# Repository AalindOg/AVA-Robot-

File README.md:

<div align="center">

# AVA — an AI companion with a physical body

**A wheeled robot project for [Half Life](https://halflife.hackclub.com) by Hack Club.**

Built by **Aalind Tiwari**, with AI-assisted CAD and development.

[Explore the CAD](cad/reference-rebuild/) · [Download STEP](https://github.com/AalindOg/AVA-Robot-/raw/refs/heads/main/cad/reference-rebuild/exports/AVA-reference-rebuild.step) · [View STL](cad/reference-rebuild/exports/AVA-reference-rebuild.stl) · [Development journal](JOURNAL.md)

*Actual renders of the current model. Not photographs of a fabricated robot.*

</div>

## What I’m building

AVA is a mobile AI companion: a screen for expression and interaction, cameras and microphones for sensing, speakers for responses, and a wheeled body. The longer-term goal is to connect that body to **Hermes Agent**, with a small controller handling the hardware interface and a computer handling higher-level processing.

This repository brings together three parts of that project: the **exterior CAD**, the **carrier-board design**, and the **firmware/server prototypes**. They are at different stages. The integrated, moving robot is not finished.

## Current milestone: a new body from the original references

The earlier STL attempt did not match the intended robot. Instead of polishing the wrong shape, this version was rebuilt from the original purple robot images and the surviving video views. The older meshes are not imported by the new model.

The design keeps the features that made the reference worth building:

- A **closed, rounded head** with a broad teal screen and thick bezel.
- Circular side grilles, flat antenna tabs and a low roof-mounted sensor housing.
- A curved torso with a narrower upper section, rounded lower body and dark panel trim.
- Two large treaded wheels with swept-spoke hubs.
- A small central twin-wheel caster, short side pods and a circular chest detail.

*Reference and reconstruction side by side. Fine seams, hidden surfaces and small hardware details are still approximate.*

> [!IMPORTANT]
> **This is an exterior design prototype, not a print-ready robot kit.** The STL files are real geometry exports, but the dimensions are image-based assumptions. Motor mounts, electronics packaging, joints, tolerances and print orientations still need engineering and physical tests. Do not print the complete assembly expecting a working robot.

## Get the files

| File | Use it for |
| --- | --- |
| [**Full STEP assembly**](https://github.com/AalindOg/AVA-Robot-/raw/refs/heads/main/cad/reference-rebuild/exports/AVA-reference-rebuild.step) | Import named, coloured solid components into FreeCAD, Fusion or Onshape. |
| [**Full STL assembly**](cad/reference-rebuild/exports/AVA-reference-rebuild.stl) | Inspect the complete geometry; this is a multi-component assembly, not one fused print. |
| [**Individual STL components**](cad/reference-rebuild/exports/parts/) | Inspect or modify separate shell sections, wheels, trim and other components. |
| [**Coloured GLB model**](https://github.com/AalindOg/AVA-Robot-/raw/refs/heads/main/cad/reference-rebuild/exports/AVA-reference-rebuild.glb) | Open in a compatible 3D viewer. Uses metres and +Y up. |
| [**CadQuery source**](cad/reference-rebuild/cad/build_robot.py) | Edit the construction and regenerate the geometry. |
| [**Design notes**](cad/reference-rebuild/DESIGN-NOTES.md) | Read the assumptions, interpretation choices and verification scope. |
| [**Printing status**](cad/reference-rebuild/PRINTING.md) | See what must be resolved before a physical prototype. |

For everything, use GitHub’s **Code → Download ZIP**, or clone this repository. STEP/STL use millimetres. STEP contains editable solids; the procedural construction lives in the Python source, not a native CAD feature-history tree.

## What has actually been checked

The current CAD export contains **38 component instances**. They include visual stand-ins for screens, sensors and axles—not 38 fabrication-ready parts.

| Check | Recorded result | Evidence |
| --- | --- | --- |
| Solid geometry | All 38 component instances valid, with positive volume | [Geometry report](cad/reference-rebuild/exports/validation.json) |
| Component clashes | No intersections above the **0.5 mm³** reporting threshold; no check errors | [Pairwise check](cad/reference-rebuild/exports/validation.json) |
| STL quality | Every individual STL is watertight, consistently wound, finite and positive-volume | [Mesh report](cad/reference-rebuild/exports/mesh-validation.json) |
| STEP round trip | Re-imported successfully; solid count and volume comparison passed | [Round-trip result](cad/reference-rebuild/exports/mesh-validation.json) |
| Viewer export | GLB re-imported with all 38 components | [Viewer check](cad/reference-rebuild/exports/mesh-validation.json) |
| Visual review | Front and angled views compared with the approved images | [Comparison sheet](cad/reference-rebuild/images/reference-comparison.jpg) |

The assumed exterior envelope is approximately **232 × 147 × 394 mm** (width × depth × height). Head width was set to **190 mm** as a scaling choice, not a measurement from a physical robot.

**These checks establish coherent files. They do not establish strength, stability, printability, electronics fit or successful motion.**

### What changed during this iteration

- Closed the head rather than reproducing the rejected open-top shape.
- Refined the lower-body curve, screen opening, wheel scale, antenna angle and sensor placement against the references.
- Replaced side-pod geometry that produced non-watertight STL exports.
- Fixed a shell-splitting operation that returned an empty result despite reporting valid topology.
- Used matching numerical integration tolerances when comparing STEP export/import volumes.

The useful outcome is not just a better render: the source, exported solids and validation reports are all here to inspect.

## Carrier board and electronics

The existing v1 carrier-board design is retained alongside the new CAD. It includes a battery input and power switching, a buck-module connection, a TB6612FNG motor-driver module socket, a XIAO ESP32-S3 Sense socket, motor connectors and an I²C expansion connector.

- [KiCad schematic](hardware/ava-carrier.kicad_sch)
- [Schematic PDF](hardware/ava-carrier-schematic.pdf)
- [KiCad PCB layout](hardware/ava-carrier.kicad_pcb)
- [Gerber and drill package](hardware/fabrication/ava-carrier-v1-gerbers.zip)
- [Carrier-board BOM](bom.csv)

**The carrier board and the new enclosure have not been physically integrated or fit-tested.** The board files and fabrication exports are design artifacts, not evidence that a board was manufactured or powered successfully. Check component ratings and footprints before ordering or connecting a battery.

The [CAD component inventory](cad/reference-rebuild/bom.csv) is separate from the electronics BOM: it lists visual model instances, not parts to purchase.

## Software direction

The repository also retains:

- [`firmware/`](firmware/) — PlatformIO/Arduino sources for the ESP32-S3 sensing and bridge work.
- [`server/`](server/) — Python audio-receiver, transcription, dashboard and intelligence experiments.

The intended division is simple: the controller handles device I/O; the computer handles processing and agent behaviour. These are **prototype sources**, not proof of a working end-to-end robot. Their runtime and physical integration were not revalidated as part of this CAD update.

## Rebuild the CAD

Tested with Python 3.12 and CadQuery 2.8.0. From the repository root on Linux/macOS:

```sh
cd cad/reference-rebuild
python3 -m venv .venv
.venv/bin/python -m pip install -r requirements.txt

# Generate parts, assembly and geometry checks
.venv/bin/python cad/build_robot.py

# Check all meshes, re-import STEP and export GLB
.venv/bin/python cad/validate_meshes.py

# Render the actual exported geometry and compare with references
.venv/bin/python cad/render_robot.py
.venv/bin/python cad/compare.py
```

The model is editable procedural CAD, not a fully constrained configurator. Major dimensional changes also require checking the inner shell, openings and neighbouring components. Rerun the checks after edits. More details: [CAD README](cad/reference-rebuild/README.md).

## Next steps toward a physical robot

- [ ] Select and measure the actual display, motors, battery and controller boards.
- [ ] Add motor mounts, bearings, electronics mounts and battery retention.
- [ ] Design shell fasteners and access to the hardware inside.
- [ ] Resolve the caster mount, swivel clearance and wheel-to-shaft interfaces.
- [ ] Check wiring paths, ventilation and battery/power safety.
- [ ] Slice individual parts and print fit-test pieces before a full enclosure.
- [ ] Assemble, test movement and connect the hardware to the software stack.

## Half Life journal and credits

The [development journal](JOURNAL.md) and [funding tracker](BOM.md) are mirrored from [Half Life](https://halflife.hackclub.com). Those files are managed by the platform; this update leaves them unchanged. The CAD rebuild is documented here and in [design notes](cad/reference-rebuild/DESIGN-NOTES.md), rather than inventing hours or modifying past entries.

**AI assistance is part of this work.** Aalind selected the reference design, rejected the earlier model and directed the rebuild. Ava/Hermes assisted with procedural CAD generation, debugging, validation, rendering and documentation. This repository does not claim the generated work was completed unaided, that it has already been accepted for a particular week, or that the physical robot has been built.

The source images are kept separately in [references](cad/reference-rebuild/references/) so readers can distinguish the design references from the new model renders. [Provenance notes](cad/reference-rebuild/references/provenance.json) describe the surviving source copies; their original author/license is not independently established here.

## Repository map

```text
cad/reference-rebuild/
├── cad/                # Build, render, compare, validate and package scripts
├── exports/            # STEP, STL, GLB, inventory and validation reports
│   └── parts/          # Individual component-instance STLs
├── images/             # Current renders and reference comparison
├── references/         # Source reference views, kept distinct from outputs
├── DESIGN-NOTES.md
└── PRINTING.md
hardware/               # Existing carrier schematic, PCB and fabrication exports
firmware/               # Existing microcontroller prototypes
server/                 # Existing Python prototypes
bom.csv                 # Carrier-board parts list
BOM.md                  # Half Life-managed funding tracker
JOURNAL.md              # Half Life-managed devlog
```

## License and reference assets

The project’s existing MIT declaration applies to its original code and design contributions. Supplied reference images are **not** being relicensed by this update; their provenance and usage rights should be checked before reuse outside this project.

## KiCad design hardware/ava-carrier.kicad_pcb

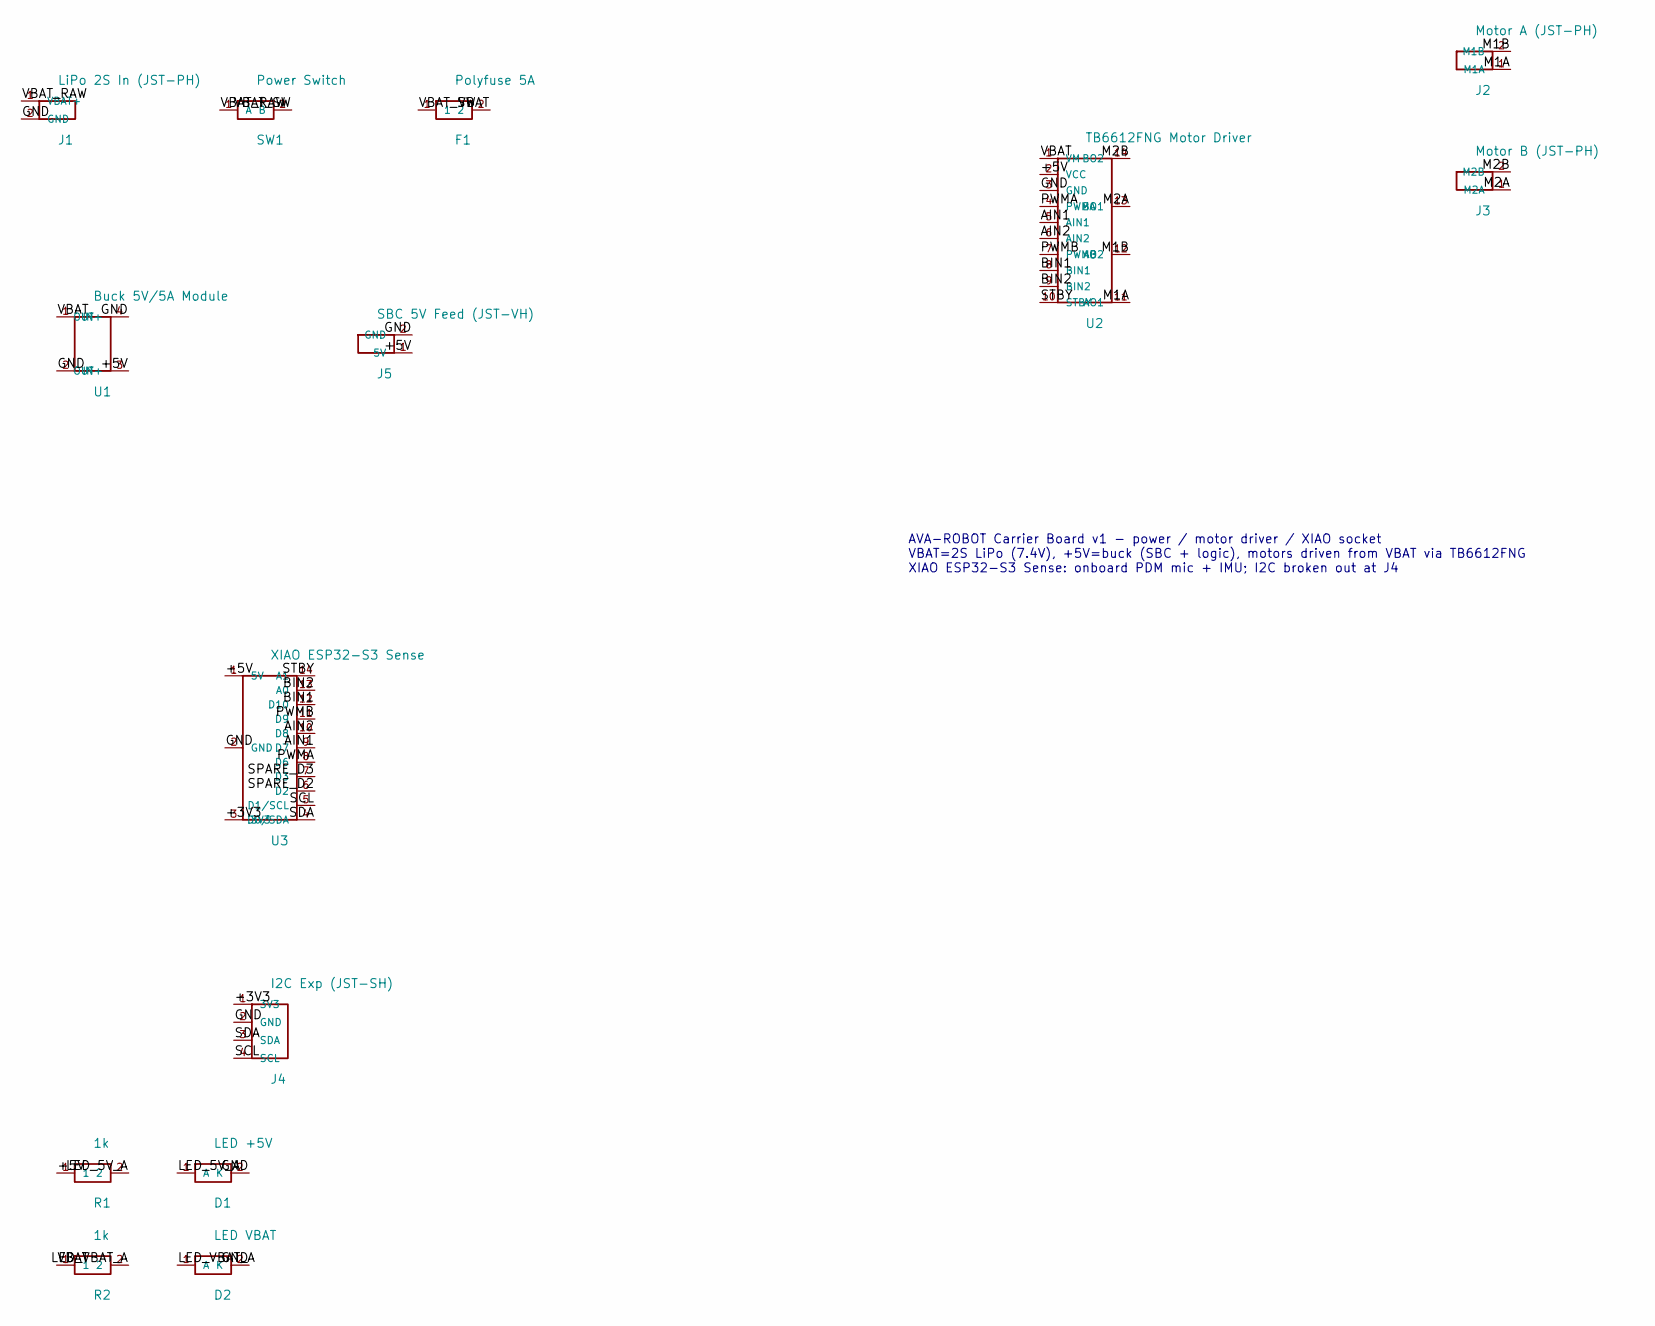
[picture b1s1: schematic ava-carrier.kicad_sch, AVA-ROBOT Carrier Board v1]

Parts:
D1: LED +5V; LED_D3.0mm
D2: LED VBAT; LED_D3.0mm
F1: Polyfuse 5A; R_Axial_DIN0207_L6.3mm_D2.5mm_P10.16mm_Horizontal
J1: LiPo 2S In (JST-PH); JST_PH_B2B-PH-K_1x02_P2.00mm_Vertical
J2: Motor A (JST-PH); JST_PH_B2B-PH-K_1x02_P2.00mm_Vertical
J3: Motor B (JST-PH); JST_PH_B2B-PH-K_1x02_P2.00mm_Vertical
J4: I2C Exp (JST-SH); JST_SH_BM04B-SRSS-TB_1x04_P1.00mm_Vertical
J5: SBC 5V Feed (JST-VH); JST_VH_B2P-VH-B_1x02_P3.96mm_Vertical
R1, R2: 1k; R_Axial_DIN0207_L6.3mm_D2.5mm_P10.16mm_Horizontal
SW1: Power Switch; SW_Slide_1P2T_CK_OS102011MA1QN1
U1: Buck 5V/5A Module; PinHeader_1x04_P2.54mm_Vertical
U2: TB6612FNG Motor Driver; PinHeader_2x08_P2.54mm_Vertical
U3: XIAO ESP32-S3 Sense; SeeedStudio_XIAO_ESP32-S3_Socket

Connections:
+3V3: J4.1 (3V3), U3.3 (3V3)
+5V: J5.1 (5V), R1.1, U1.3 (OUT+), U2.2 (VCC), U3.1 (5V)
AIN1: U2.5 (AIN1), U3.9 (D7)
AIN2: U2.6 (AIN2), U3.10 (D8)
BIN1: U2.8 (BIN1), U3.12 (D10)
BIN2: U2.9 (BIN2), U3.13 (A0)
GND: D1.2 (K), D2.2 (K), J1.2 (GND), J4.2 (GND), J5.2 (GND), U1.2 (IN-), U1.4 (OUT-), U2.3 (GND), U3.2 (GND)
LED_5V_A: D1.1 (A), R1.2
LED_VBAT_A: D2.1 (A), R2.2
M1A: J2.1 (M1A), U2.11 (AO1)
M1B: J2.2 (M1B), U2.12 (AO2)
M2A: J3.1 (M2A), U2.13 (BO1)
M2B: J3.2 (M2B), U2.14 (BO2)
PWMA: U2.4 (PWMA), U3.8 (D6)
PWMB: U2.7 (PWMB), U3.11 (D9)
SCL: J4.4 (SCL), U3.5 (D1/SCL)
SDA: J4.3 (SDA), U3.4 (D0/SDA)
SPARE_D2: U3.6 (D2)
SPARE_D3: U3.7 (D3)
STBY: U2.10 (STBY), U3.14 (A1)
VBAT: F1.2, R2.1, U1.1 (IN+), U2.1 (VM)
VBAT_RAW: J1.1 (VBAT+), SW1.1 (A)
VBAT_SW: F1.1, SW1.2 (B)

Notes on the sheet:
AVA-ROBOT Carrier Board v1 - power / motor driver / XIAO socket VBAT=2S LiPo (7.4V), +5V=buck (SBC + logic), motors driven from VBAT via TB6612FNG XIAO ESP32-S3 Sense: onboard PDM mic + IMU; I2C broken out at J4

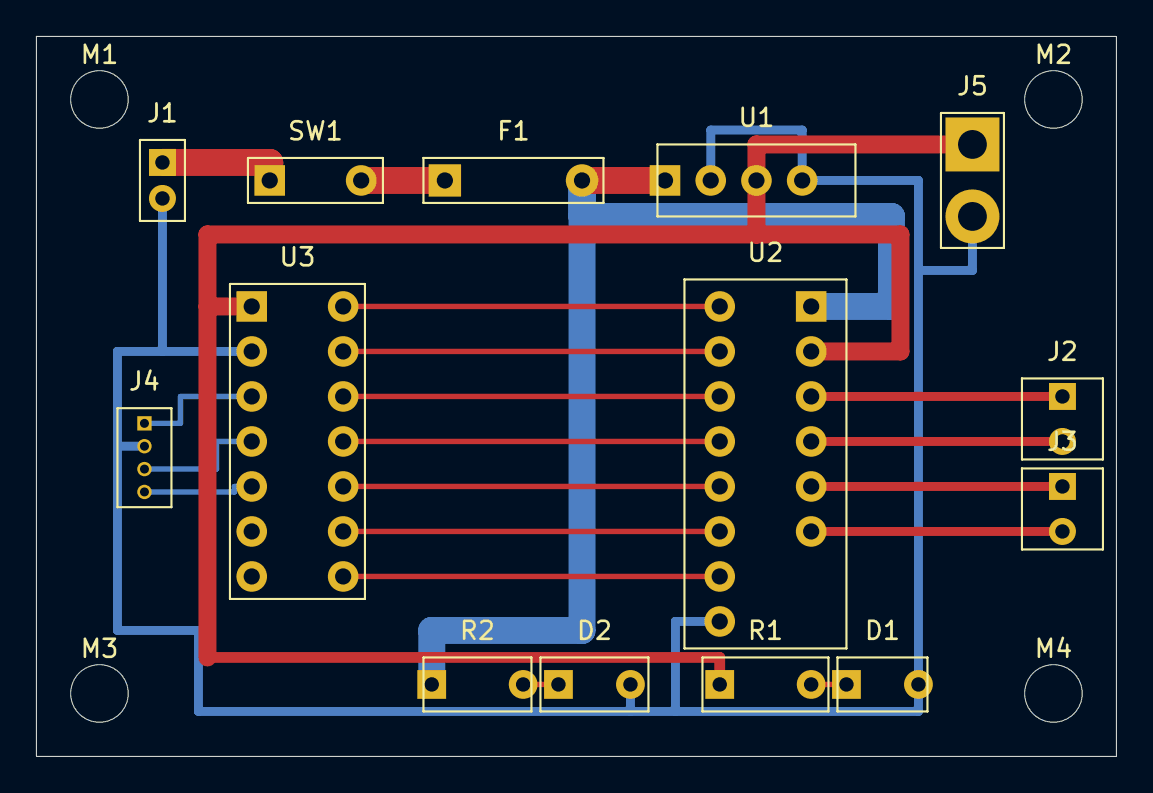
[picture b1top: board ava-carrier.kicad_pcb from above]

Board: 2 copper layers, 60.0 x 40.0 mm, 18 parts (0 on the bottom side), 21 nets.

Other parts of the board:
M1, M2, M3, M4: M3; MOUNT_M3

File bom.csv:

Ref,Qty,Value,Part,Footprint,Notes
J1,1,LiPo 2S Input,JST-PH B2B-PH-K (2 pos),Connector_JST:JST_PH_B2B-PH-K_1x02_P2.00mm_Vertical,7.4V 2S battery input
SW1,1,Power Switch,CK OS102011 slide switch,Button_Switch:SW_Slide_1P2T_CK_OS102011MA1QN1,Main power
F1,1,Polyfuse 5A,Raychem miniSMDC050 or equiv,Resistor:R_Axial_DIN0207,Resettable fuse on VBAT
U1,1,Buck 5V/5A,Mini-560 style buck module (socket),Connector:PinHeader_1x04_P2.54mm_Vertical,VBAT to +5V; powers SBC + logic
U2,1,TB6612FNG Motor Driver,TB6612FNG breakout module (socket),Connector:PinHeader_2x08_P2.54mm_Vertical,Dual 1.2A motor driver; VM=VBAT
U3,1,XIAO ESP32-S3 Sense,Seeed Studio XIAO ESP32-S3 Sense,Module:SeeedStudio_XIAO_ESP32-S3_Socket,Audio bridge + IMU + motor control GPIOs
J2,1,Motor A,JST-PH B2B-PH-K (2 pos),Connector_JST:JST_PH_B2B-PH-K_1x02_P2.00mm_Vertical,Left drive motor
J3,1,Motor B,JST-PH B2B-PH-K (2 pos),Connector_JST:JST_PH_B2B-PH-K_1x02_P2.00mm_Vertical,Right drive motor
J4,1,I2C Expansion,JST-SH BM04B-SRSS-TB (4 pos),Connector_JST:JST_SH_BM04B-SRSS-TB_1x04_P1.00mm_Vertical,Qwiic-style: 3V3 GND SDA SCL
J5,1,SBC 5V Feed,JST-VH B2P-VH (2 pos),Connector_JST:JST_VH_B2P-VH-B_1x02_P3.96mm_Vertical,5V power to single-board computer
R1,1,1k,1kOhm 1/4W resistor,Resistor:R_Axial_DIN0207,LED series resistor (+5V rail)
R2,1,1k,1kOhm 1/4W resistor,Resistor:R_Axial_DIN0207,LED series resistor (VBAT rail)
D1,1,LED +5V,Green LED 3mm,LED:LED_D3.0mm,5V rail indicator
D2,1,LED VBAT,Red LED 3mm,LED:LED_D3.0mm,Battery rail indicator
